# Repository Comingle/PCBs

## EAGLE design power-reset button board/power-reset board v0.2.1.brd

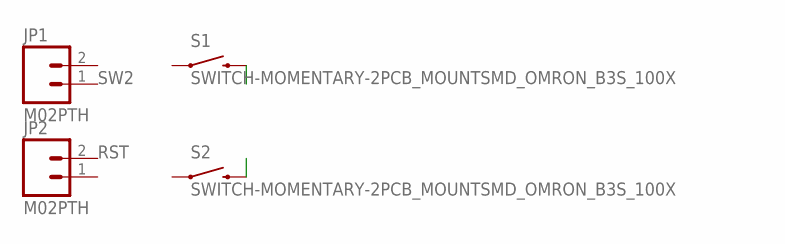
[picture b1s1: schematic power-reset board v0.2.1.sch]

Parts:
JP1, JP2: M02PTH; 1X02
S1, S2: SWITCH-MOMENTARY-2PCB_MOUNTSMD_OMRON_B3S_100X; TACTILE_SWITCH_LARGE

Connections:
GND: JP2.1, S2.1
RST: JP2.2, S2.3 (2)
SW1: JP1.2, S1.1
SW2: JP1.1, S1.3 (2)

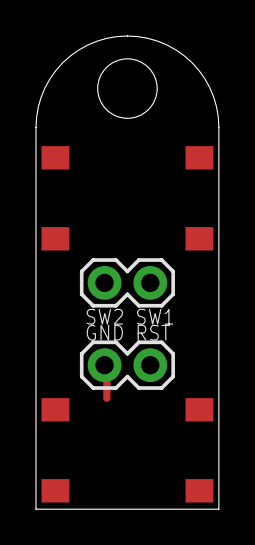
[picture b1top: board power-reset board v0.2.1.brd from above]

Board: 2 copper layers, 10.2 x 26.3 mm, 5 parts (0 on the bottom side), 4 nets.

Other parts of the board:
U$1: STAND-OFF

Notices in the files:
parts and their libraries:
SparkFun-Electromechanical: Licensing: Creative Commons ShareAlike 4.0 International - https://creativecommons.org/licenses/by-sa/4.0
